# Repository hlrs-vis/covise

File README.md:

Table of Contents
=================

* [Software in This Repository](#software-in-this-repository)
   * [COVISE and OpenCOVER](#covise-and-opencover)
   * [Other Software](#other-software)
* [License](#license)
* [Support &amp; Mailing Lists](#support--mailing-lists)
* [Getting Binaries and Automated Installation](#getting-binaries-and-automated-installation)
   * [macOS](#macos)
   * [Windows](#windows)
* [Getting the Source Code](#getting-the-source-code)
   * [UNIX and Command Line](#unix-and-command-line)
   * [Working with Git](#working-with-git)
      * [UNIX](#unix)
* [Building COVISE and OpenCOVER](#building-covise-and-opencover)
   * [Build Requirements](#build-requirements)
   * [Optional Dependencies](#optional-dependencies)
   * [Tracking Dependencies](#tracking-dependencies)
   * [Directory for Third Party Dependencies](#directory-for-third-party-dependencies)
   * [Building on UNIX](#building-on-unix)
      * [Building only OpenCOVER](#building-only-opencover)
      * [Building only Oddlot](#building-only-oddlot)
   * [Building on Windows](#building-on-windows)
      * [Building with VS Code](#building-with-code)
   * [Changing CMake Settings](#changing-cmake-settings)
* [Building Documentation](#building-documentation)
* [Invoking COVISE](#invoking-covise)
   * [UNIX](#unix-1)
   * [Windows](#windows-1)
* [Source Code Organization](#source-code-organization)

Software in This Repository
===========================

COVISE and OpenCOVER
--------------------

[COVISE][1], the collaborative visualization and simulation environment, is a modular distributed visualization system.
As its focus is on visualization of scientific data in virtual environments, it comprises the VR renderer [OpenCOVER][2].
COVISE development is headed by [HLRS][3].
It is portable to Windows and UNIX. We do regular builds on x86_64 Windows, Linux and macOS.

Other Software
--------------
Also included in this repository are [OddLOT][8], an OpenDRIVE editor, as well as vrmlExp, a VRML97 and X3D exporter for Autodesk 3ds Max.

License
=======

If not stated otherwise, the source code in this repository is licensed under the LGPL v2.1.
See `lgpl-2.1.txt` for details.

Support & Mailing Lists
=======================

As a user of COVISE, you might get answers to your questions on the [covise-users][4] mailing list.
Please direct any questions related to installing/building/using COVISE there.

You can receive notifications of changes to COVISE on the [covise-commits][5] list.

Getting Binaries and Automated Installation
===========================================

If you need OddLOT only, please have a look at [https://github.com/hbanzhaf/docker_covise][9].

macOS
-----

There is a [Homebrew][6] formula for COVISE. If you have it on your system, then you can simply

      brew install hlrs-vis/tap/covise

This will install COVISE, OpenCOVER, and OddLOT with all their dependencies.

Windows
-------

Windows binaries, which include COVISE, OpenCOVER and OddLOT, can be found on the [COVISE download page][7].
A separate installer for the VRML exporter vrmlExp is also available on the same webpage.

Getting the Source Code
=======================

UNIX and Command Line
---------------------

Getting COVISE is as easy as

      git clone https://github.com/hlrs-vis/covise.git --recursive

Update your existing copy to the current version by

      git pull -r
      git submodule sync --recursive
      git submodule update --init --recursive # update submodules to latest required version

Working with Git
---------------

### UNIX
      cd covise
      git pull -r #-r requests a rebase of your changes to avoid trivial branching
      git submodule update --init --recursive # update submodules to latest required version

Building COVISE and OpenCOVER
=============================

Build Requirements
------------------

The script `scripts/install-deps.sh` will help you to install the dependencies
provided by your Linux distribution (Debian/Ubuntu and RHEL/CentOS).

- **C++ compiler**:
  C++11

  On Windows, we currently use Visual Studio 2022 (VC17).
  GCC 5.3 and newer should work.

- **CMake**:
  3.1 or newer is required, but currently we suggest CMake 3.7 or newer
- **XercesC**:
- **Qt**:
  Qt 5 or 6 is required by the graphical user interface.
  Not everything, most importantly OddLOT, works with Qt 6 yet.

  For Qt5, you need the following modules:
    - `Qt5Core`
    - `Qt5Network`
    - `Qt5Xml`
    - `Qt5Widgets`
    - `Qt5OpenGL`
    - `Qt5WebKit`
    - `Qt5WebKitWidgets`
    - `Qt5Gui`
    - `Qt5Svg`
    - `Qt5PrintSupport`
    - `Qt5UiTools`
    - `Qt5Script`
    - `Qt5ScriptTools`

  On Ubuntu 14.04, you should be able to install the required packages with
  this command:
  `sudo apt-get install qttools5-dev qtscript5-dev libqt5scripttools5 libqt5svg5-dev libqt5opengl5-dev libqt5webkit5-dev`

- **Boost**:
  1.52 and newer should work, following boost libraries are required:
    - `chrono`
    - `date-time`
    - `filesystem`
    - `iostreams`
    - `locale`
    - `program-options`
    - `regex`
    - `serialization`
    - `system`
    - `thread`
  When any of these are missing, you will only get a generic message, that "Boost" is missing. Thus beware!
  Ubuntu 14.04: `sudo apt-get install libboost-all-dev`
- **Python**:
  Python 3 is required for the GUI vr-prepare and for the scripting interface
- **GLEW**:
  Used for OpenGL extension handling in Virvo (direct volume rendering) and OpenCOVER
- **OpenSceneGraph**:
  3.2 or newer is required, 3.4 or newer highly recommended for the VR and desktop renderer OpenCOVER

Optional Dependencies
---------------------
- **JPEG Turbo**
- **VTK**
  Version 6 or newer is required.
- **Flex** and **Bison**
  Lexer/Parser generators, required to build VRML plugin.

Install dependencies on Redhat8
-------------------------------

```
dnf -y install xerces-c
dnf -y install xerces-c-devel

dnf -y install glibc-static

dnf -y install libXi-devel
dnf -y install glibc-utils

dnf -y install glut
dnf -y install glut-devel
dnf -y install boost
dnf -y install boost-devel

dnf -y install cmake   
dnf -y install cmake3  

dnf -y install qt5-qttools-devel
dnf -y install qt5-qtscript-devel
dnf -y install qt5-qtsvg-devel
dnf -y install qt5-qttools-static
dnf -y install glew-devel
dnf -y install libtiff-devel
dnf -y install qt5-qtquickcontrols
dnf -y install qt5-qtdeclarative-devel
dnf -y install qt5-qtlocation qt5-qtlocation-devel

dnf -y install boost-chrono
dnf -y install boost-date-time
dnf -y install boost-filesystem
dnf -y install boost-iostreams
dnf -y install boost-locale
dnf -y install boost-program-options
dnf -y install boost-regex
dnf -y install boost-serialization
dnf -y install boost-system
dnf -y install boost-thread
dnf --enablerepo=PowerTools install qt5-qttools-static
dnf --enablerepo=PowerTools install libGLEW
dnf --enablerepo=PowerTools install glew-devel

dnf install http://repo.okay.com.mx/centos/8/x86_64/release/okay-release-1-1.noarch.rpm
dnf install gcc-gfortran
dnf --enablerepo=PowerTools install libstdc++-static
dnf --enablerepo=PowerTools install boost-static
dnf install python3-pyqt5-sip
dnf install fuse-devel
```

Tracking Dependencies
---------------------
CMake will show lists of met and unmet optional and required dependencies.
You should check those and install additional prerequisites as needed.

Directory for Third Party Dependencies
--------------------------------------
COVISE is set up to automatically search for third party libraries in
subdirectories of a directory pointed to by the environment variable
EXTERNLIBS.
You should install e.g. OpenSceneGraph into $EXTERNLIBS/openscenegraph, and
it will be discovered during the build process.

Building on UNIX
----------------

      cd covise
      source .covise.sh #set environment variables
      make #invoke cmake followed by make

This command sequence sets environment variables necessary while building
COVISE, invokes `cmake` for the COVISE project, and builds COVISE with 
OpenCOVER.

After an initial build, it is possible to invoke `make` from within
subdirectories of `covise/src`.

No installation is required: you can use COVISE directly from the build tree.

### Building only OpenCOVER

      cd covise
      source .covise.sh #set environment variables
      COVISE_CMAKE_OPTIONS=-DCOVISE_BUILD_ONLY_COVER=ON make #invoke cmake with provided options followed by make

### Building only OddLOT

      cd covise
      source .covise.sh #set environment variables
      COVISE_CMAKE_OPTIONS=-DCOVISE_BUILD_ONLY_ODDLOT=ON make #invoke cmake with provided options followed by make

Building on Windows
-------------------
Also on Windows, you should work from a command prompt:

       REM set COVISEDIR to location of your COVISE checkout
       set COVISEDIR=c:/src/covise
	   REM set EXTERNLIBS to correct location of all your dependancies
       set EXTERNLIBSROOT=c:\src\externlibs
       cd %COVISEDIR%
	   REM call winenv.bat with appropriate archsuffix for debug or release (tamarau for Visual Studio 2012 and zebu for 2015)
       call %COVISEDIR%\winenv.bat zebuopt
       mkdir build.covise
       cd build.covise
       cmake-gui ..
       REM open Visual Studio - either directly or with the button from CMake GUI
       devenv

To create a permanent link to a covise command prompt edit and execute Scripts/installCoviseCommandPrompt.bat 

#### Building with VS Code

This is an alternative to Visual Studio. You need VS Code with the C/C++ Extension Pack installed. You also need the MSVC compiler (with ATL support) and one of the supported generators (Ninja, Visual Studio).
To configure and build COVISE:

    open the COVISE directory with VS Code
    use the command palette (ctrl + shift + p) -> Tasks: Run Task -> Configure COVISE
    fill in requested information
    select a compiler via the CMake extension (button in the bottom bar or via the command pallete -> CMake: Select a Kit)
    run CMake with a build configuration (button in the bottom bar or via the command pallete -> CMake: Configure)
    build (button in the bottom bar or via the command pallete -> CMake: Build)

After this setup VS Code's default integrated terminal is configured to load the environment required to work with COVISE.  
Additionally debug configurations to launch COVISE and OpenCOVIER or to attach to a process are provided under VS Code's debug section. InteliSense should be enabled if you are using a generator that can export compile commands (Ninja).

Changing CMake Settings
-----------------------
You can influence which parts of COVISE are built by editing CMake settings in
`${COVISEDIR}/${ARCHSUFFIX}/build.covise/CMakeCache.txt`.
This might help you work around build problems.

    cd ${COVISEDIR}/${ARCHSUFFIX}/build.covise
    ccmake ../..

- `COVISE_BUILD_ONLY_COVER`: build only the OpenCOVER VR/desktop renderer without the COVISE visualization pipeline
- `COVISE_BUILD_ONLY_ODDLOT`: build only the road editor OddLOT
- `COVISE_BUILD_DRIVINGSIM`: enable the driving simulator components of OpenCOVER
- `COVISE_USE_VIRVO`: disable support for direct volume rendering
- `COVISE_USE_CUDA`: disable use of CUDA
- `COVISE_CPU_ARCH`: set optimization for the CPU in your computer

After changing any of these settings, you have to restart the build process.

You can also provide initial CMake options by adding them to the environment `COVISE_CMAKE_OPTIONS` before calling `make`.

Building Documentation
======================

COVISE retrieves documentation from the web server at HLRS.
But you also can build the documentation locally. You need the following
tools:

- pdflatex
- latex2html
- doxygen
- graphviz
- epstopdf

Then you can:

    cd ${COVISEDIR}/doc
    make

Invoking COVISE
===============

UNIX
----

Add .../covise/bin to your PATH.

      covise

Windows
-------

COVISE can be used without installation, provided you take the same steps as
for building:

       REM set COVISEDIR to location of your COVISE checkout
       set COVISEDIR=c:/src/covise
	   REM set EXTERNLIBS to correct location of all your dependancies
       set EXTERNLIBSROOT=c:\src\externlibs
       cd %COVISEDIR%
	   REM call winenv.bat with appropriate archsuffix for debug or release (tamarau for Visual Studio 2012 and zebu for 2015 Update 3, 2017 or 2019)
       call %COVISEDIR%\winenv.bat zebuopt
       covise
       opencover

Source Code Organization
========================

- `cmake`:
  cmake files

- `doc`:
  documentation and tools for creating documentation

- `config`:
  configuration examples

- `scripts`:
  support scripts for building COVISE

- `share`:
  architecture independent files: textures, shaders, example data, ...

- `src`:
  source code

  - `src/3rdparty`:
    3rd party source code

  - `src/tools`:
    various programs related to building or using COVISE

  - `src/kernel`:
    COVISE core libraries

  - `src/sys`:
    COVISE core executables

  - `src/module`:
    COVISE visualization modules (algorithms)

  - `src/OpenCOVER`:
    VR renderer with its plug-ins

  - `src/oddlot`:
    OpenDRIVE road editor OddLOT

[1]:   http://www.hlrs.de/covise/
[2]:   http://www.hlrs.de/solutions-services/service-portfolio/visualization/covise/opencover/
[3]:   http://www.hlrs.de/
[4]:   https://listserv.uni-stuttgart.de/mailman/listinfo/covise-users
[5]:   https://listserv.uni-stuttgart.de/mailman/listinfo/covise-commits
[6]:   http://brew.sh
[7]:   https://fs.hlrs.de/projects/covise/support/download/
[8]:   http://www.hlrs.de/oddlot/
[9]:   https://github.com/hbanzhaf/docker_covise

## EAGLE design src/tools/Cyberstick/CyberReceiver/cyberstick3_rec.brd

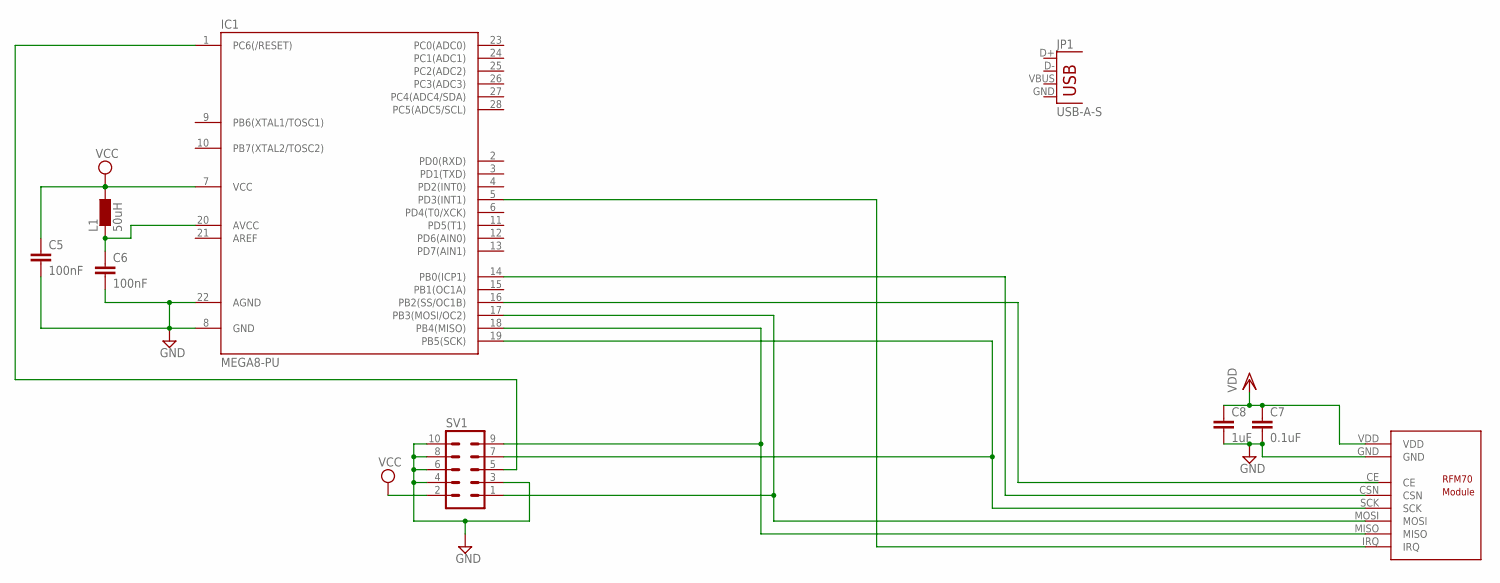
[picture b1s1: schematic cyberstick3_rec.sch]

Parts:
C5, C6: 100nF; C2.5-3
C7: 0.1uF; C2.5-3
C8: 1uF; C2.5-3
IC1: MEGA8-PU; DIL28-3
JP1: USB-A-S
L1: 50uH; 0204/7
SV1: MA05-2
U$2: RFM70

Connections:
GND: C5.2, C6.2, C7.2, C8.2, IC1.8 (GND), IC1.22 (AGND), SV1.3, SV1.4, SV1.6, SV1.8, SV1.10, U$2.GND
unnamed: IC1.5 (PD3(INT1)), U$2.IRQ
unnamed: IC1.19 (PB5(SCK)), SV1.7, U$2.SCK
unnamed: IC1.14 (PB0(ICP1)), U$2.CSN
unnamed: IC1.17 (PB3(MOSI/OC2)), SV1.1, U$2.MOSI
unnamed: IC1.1 (PC6(/RESET)), SV1.5
unnamed: IC1.18 (PB4(MISO)), SV1.9, U$2.MISO
unnamed: C6.1, IC1.20 (AVCC), L1.2
VCC: C5.1, IC1.7 (VCC), L1.1, SV1.2
VDD: C7.1, C8.1, U$2.VDD

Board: 2 copper layers, 9 parts (0 on the bottom side), 10 nets, no tracks yet.

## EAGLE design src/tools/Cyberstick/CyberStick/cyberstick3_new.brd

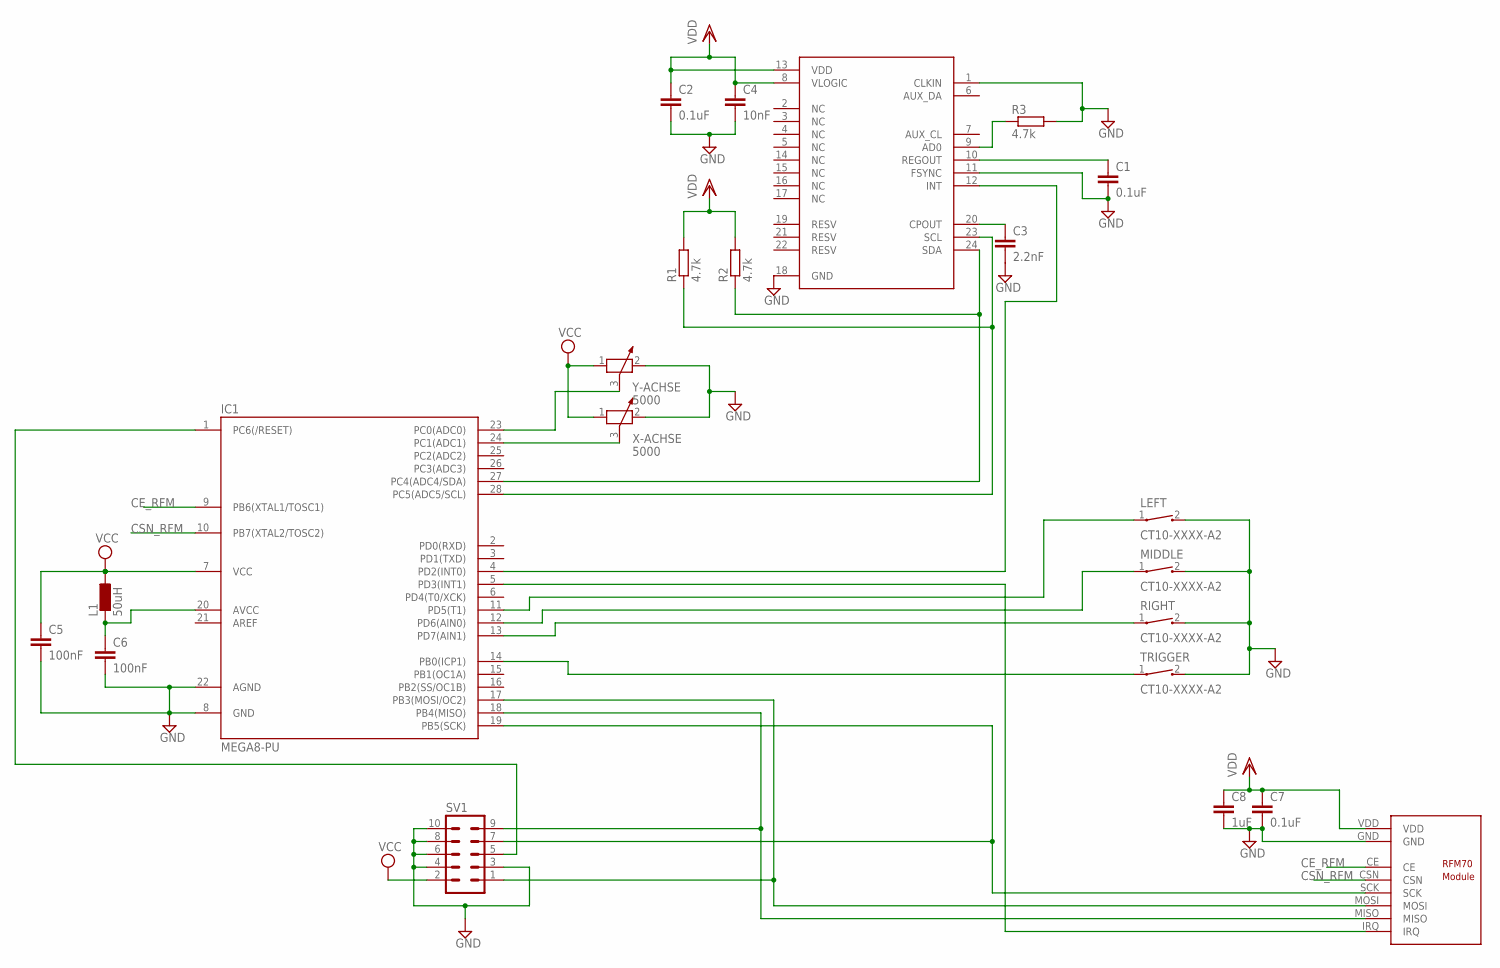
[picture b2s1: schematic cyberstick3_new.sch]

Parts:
C1, C2, C7: 0.1uF; C2.5-3
C3: 2.2nF; C2.5-3
C4: 10nF; C2.5-3
C5, C6: 100nF; C2.5-3
C8: 1uF; C2.5-3
IC1: MEGA8-PU; DIL28-3
L1: 50uH; 0204/7
LEFT: CT10-XXXX-A2
MIDDLE: CT10-XXXX-A2
R1, R2, R3: 4.7k; 0204/7
RIGHT: CT10-XXXX-A2
SV1: MA05-2
TRIGGER: CT10-XXXX-A2
U1: MPU6050
U$2: RFM70
X-ACHSE: 5000; PT-10
Y-ACHSE: 5000; PT-10

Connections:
CE_RFM: IC1.9 (PB6(XTAL1/TOSC1)), U$2.CE
CSN_RFM: IC1.10 (PB7(XTAL2/TOSC2)), U$2.CSN
GND: C1.2, C2.2, C3.2, C4.2, C5.2, C6.2, C7.2, C8.2, IC1.8 (GND), IC1.22 (AGND), LEFT.2, MIDDLE.2, R3.2, RIGHT.2, SV1.3, SV1.4, SV1.6, SV1.8, SV1.10, TRIGGER.2, U1.1 (CLKIN), U1.11 (FSYNC), U1.18 (GND), U$2.GND, X-ACHSE.2, Y-ACHSE.2
unnamed: IC1.14 (PB0(ICP1)), TRIGGER.1
unnamed: IC1.4 (PD2(INT0)), U1.12 (INT)
unnamed: IC1.19 (PB5(SCK)), SV1.7, U$2.SCK
unnamed: IC1.13 (PD7(AIN1)), RIGHT.1
unnamed: IC1.24 (PC1(ADC1)), X-ACHSE.3
unnamed: IC1.23 (PC0(ADC0)), Y-ACHSE.3
unnamed: IC1.17 (PB3(MOSI/OC2)), SV1.1, U$2.MOSI
unnamed: IC1.1 (PC6(/RESET)), SV1.5
unnamed: IC1.27 (PC4(ADC4/SDA)), R2.1, U1.24 (SDA)
unnamed: IC1.12 (PD6(AIN0)), MIDDLE.1
unnamed: C3.1, U1.20 (CPOUT)
unnamed: C1.1, U1.10 (REGOUT)
unnamed: IC1.18 (PB4(MISO)), SV1.9, U$2.MISO
unnamed: IC1.28 (PC5(ADC5/SCL)), R1.1, U1.23 (SCL)
unnamed: IC1.11 (PD5(T1)), LEFT.1
unnamed: C6.1, IC1.20 (AVCC), L1.2
unnamed: IC1.5 (PD3(INT1)), U$2.IRQ
unnamed: R3.1, U1.9 (AD0)
VCC: C5.1, IC1.7 (VCC), L1.1, SV1.2, X-ACHSE.1, Y-ACHSE.1
VDD: C2.1, C4.1, C7.1, C8.1, R1.2, R2.2, U1.8 (VLOGIC), U1.13 (VDD), U$2.VDD

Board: 2 copper layers, 22 parts (0 on the bottom side), 23 nets, no tracks yet.

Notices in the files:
parts and their libraries:
SparkFun-Connectors: Licensing: Creative Commons ShareAlike 4.0 International - https://creativecommons.org/licenses/by-sa/4.0
